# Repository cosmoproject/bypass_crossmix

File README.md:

# bypass_crossmix
Relay stereo bypass and crossmixer

Crossmixer connection: Turn the pot completely to what you want to be "wet", and find the side where
there is 0ohm to the center pin. This pin should be connected to pin 1 on the drywet on the PCB.

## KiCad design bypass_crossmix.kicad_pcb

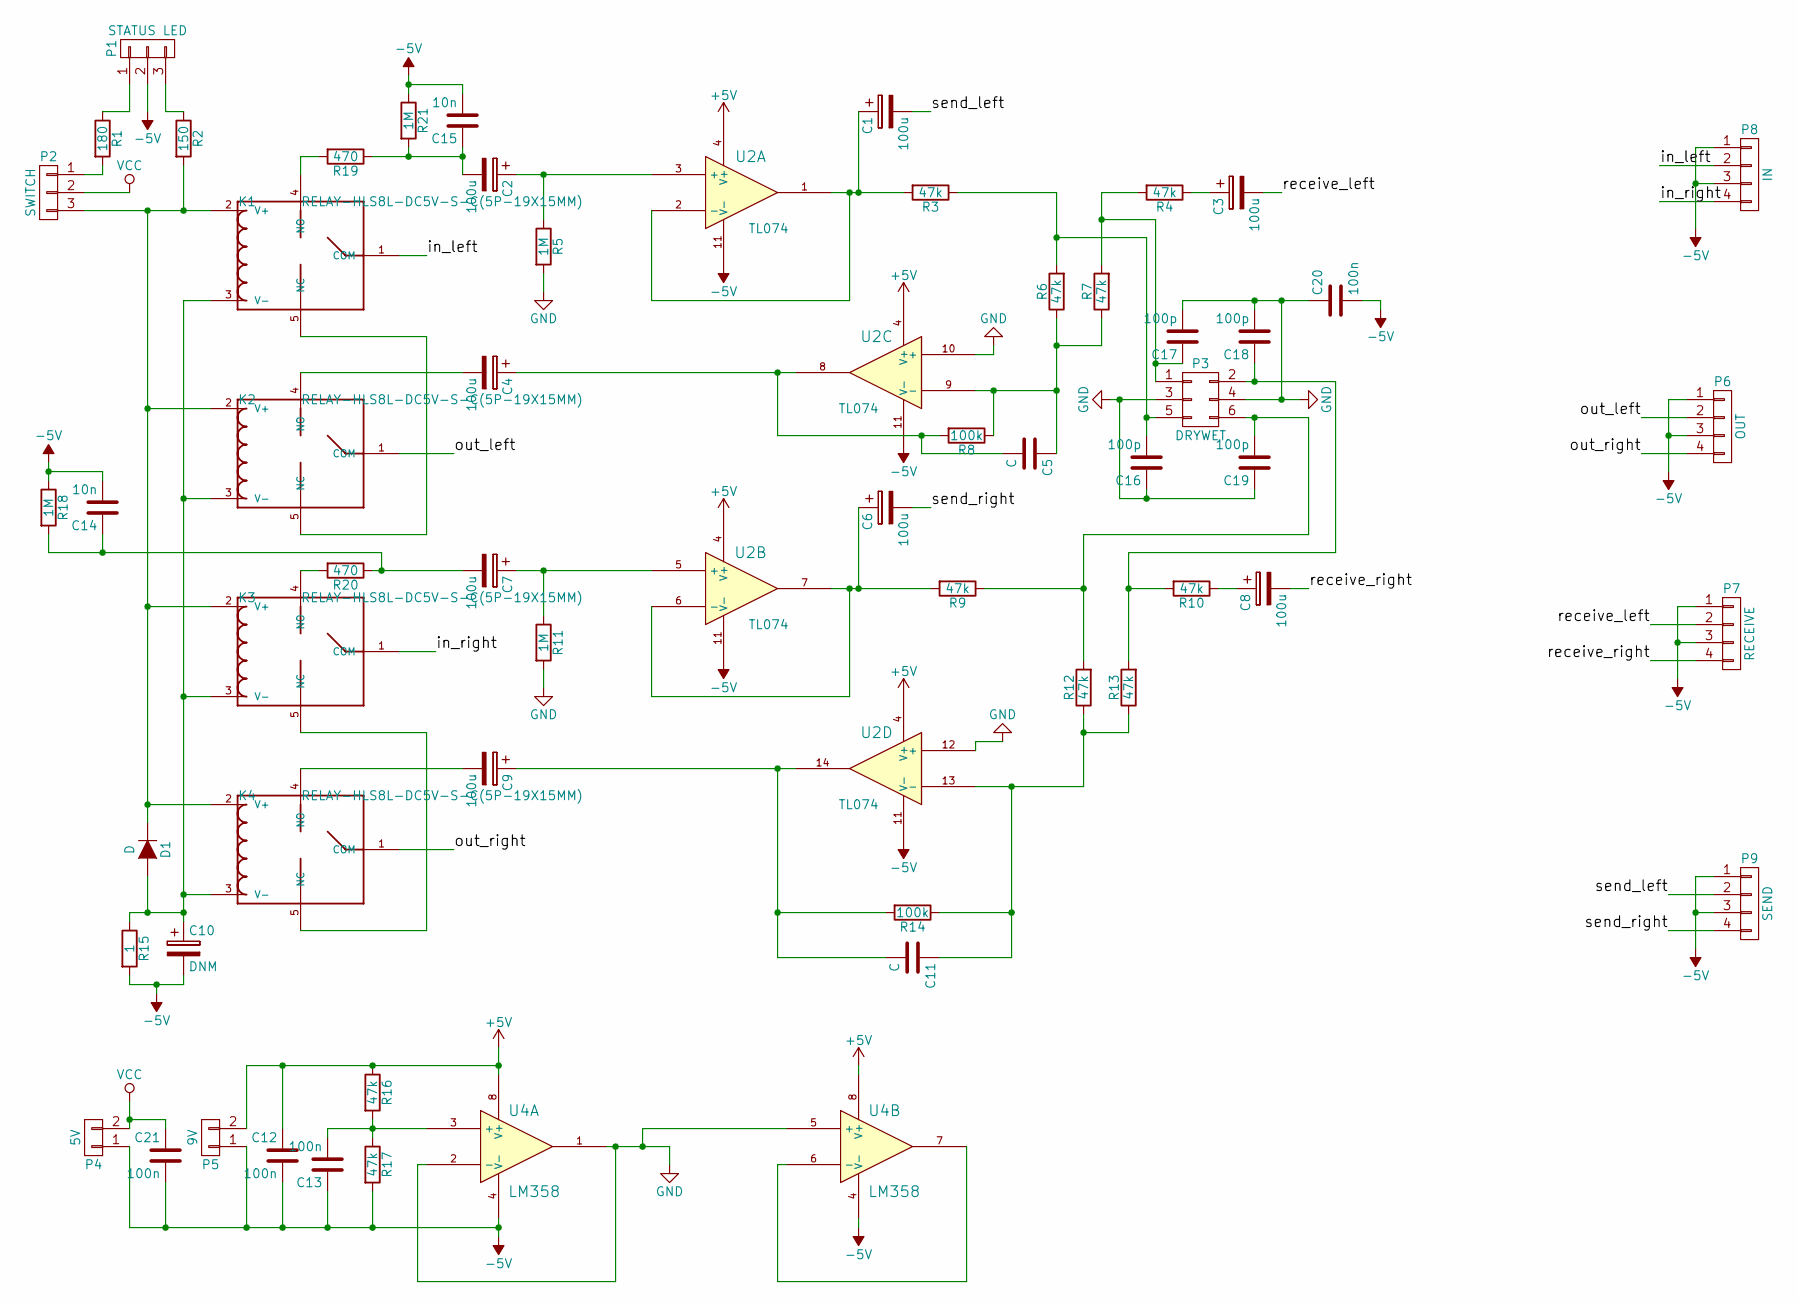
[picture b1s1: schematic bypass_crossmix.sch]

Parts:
C1, C2, C3, C4, C6, C7, C8, C9: 100u; Elko_vert_11x5mm_RM2.5_CopperClear
C5, C11: C; C_0603_HandSoldering
C10: DNM; Elko_vert_11x5mm_RM2.5_CopperClear
C12, C13, C20, C21: 100n; C_0603_HandSoldering
C14, C15: 10n; C_0603_HandSoldering
C16, C17, C18, C19: 100p; C_0603_HandSoldering
D1: D; DO-214AC
K1, K2, K3, K4: RELAY-HLS8L-DC5V-S-C(5P-19X15MM); REY5-19.0X15.0X15.0MM
P1: STATUS LED; Pin_Header_Straight_1x03
P2: SWITCH; Pin_Header_Straight_1x03
P3: DRYWET; Pin_Header_Straight_2x03
P4: 5V; Pin_Header_Straight_1x02
P5: 9V; Pin_Header_Straight_1x02
P6: OUT; Pin_Header_Straight_1x04
P7: RECEIVE; Pin_Header_Straight_1x04
P8: IN; Pin_Header_Straight_1x04
P9: SEND; Pin_Header_Straight_1x04
R1: 180; R_0603_HandSoldering
R2: 150; R_0603_HandSoldering
R3, R4, R6, R7, R9, R10, R12, R13, R16, R17: 47k; R_0603_HandSoldering
R5, R11, R18, R21: 1M; R_0603_HandSoldering
R8, R14: 100k; R_0603_HandSoldering
R15: 1; R_0603_HandSoldering
R19, R20: 470; R_0603_HandSoldering
U2: TL074; SOIC-14_3.9x8.7mm_Pitch1.27mm
U4: LM358; SOIC-8_3.9x4.9mm_Pitch1.27mm

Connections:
+5V: C12.1, P5.2, R16.1, U2.4 (V+), U4.8 (V+)
-5V: C10.2, C12.2, C13.1, C14.2, C15.2, C20.2, C21.2, P1.2, P4.1, P5.1, P6.1, P6.3, P7.1, P7.3, P8.1, P8.3, P9.1, P9.3, R15.2, R17.2, R18.1, R21.1, U2.11 (V-), U4.4 (V-)
/in_left: K1.1 (COM), P8.2
/in_right: K3.1 (COM), P8.4
/out_left: K2.1 (COM), P6.2
/out_right: K4.1 (COM), P6.4
/receive_left: C3.2, P7.2
/receive_right: C8.2, P7.4
/send_left: C1.2, P9.2
/send_right: C6.2, P9.4
GND: C16.1, C17.2, C18.2, C19.1, C20.1, P3.3, P3.4, R5.2, R11.2, U2.10 (+), U2.12 (+), U4.1, U4.2 (-), U4.5 (+)
unnamed: C1.1, R3.2, U2.1, U2.2 (-)
unnamed: C2.1, R5.1, U2.3 (+)
unnamed: C3.1, R4.1
unnamed: C4.1, C5.2, R8.2, U2.8
unnamed: C4.2, K2.4 (NO)
unnamed: C5.1, R6.1, R7.1, R8.1, U2.9 (-)
unnamed: C6.1, R9.2, U2.6 (-), U2.7
unnamed: C7.1, R11.1, U2.5 (+)
unnamed: C8.1, R10.1
unnamed: C9.2, K4.4 (NO)
unnamed: C10.1, D1.2 (A), K1.3 (V-), K2.3 (V-), K3.3 (V-), K4.3 (V-), R15.1
unnamed: C11.1, R12.1, R13.1, R14.1, U2.13 (-)
unnamed: C9.1, C11.2, R14.2, U2.14
unnamed: C13.2, R16.2, R17.1, U4.3 (+)
unnamed: C7.2, C14.1, R18.2, R20.1
unnamed: C2.2, C15.1, R19.1, R21.2
unnamed: C16.2, P3.5, R3.1, R6.2
unnamed: C17.1, P3.1, R4.2, R7.2
unnamed: C18.1, P3.2, R10.2, R13.2
unnamed: C19.2, P3.6, R9.1, R12.2
unnamed: D1.1 (K), K1.2 (V+), K2.2 (V+), K3.2 (V+), K4.2 (V+), P2.3, R2.2
unnamed: K1.4 (NO), R19.2
unnamed: K1.5 (NC), K2.5 (NC)
unnamed: K3.4 (NO), R20.2
unnamed: K3.5 (NC), K4.5 (NC)
unnamed: P1.1, R1.1
unnamed: P1.3, R2.1
unnamed: P2.1, R1.2
unnamed: U4.6 (-), U4.7
VCC: C21.1, P2.2, P4.2

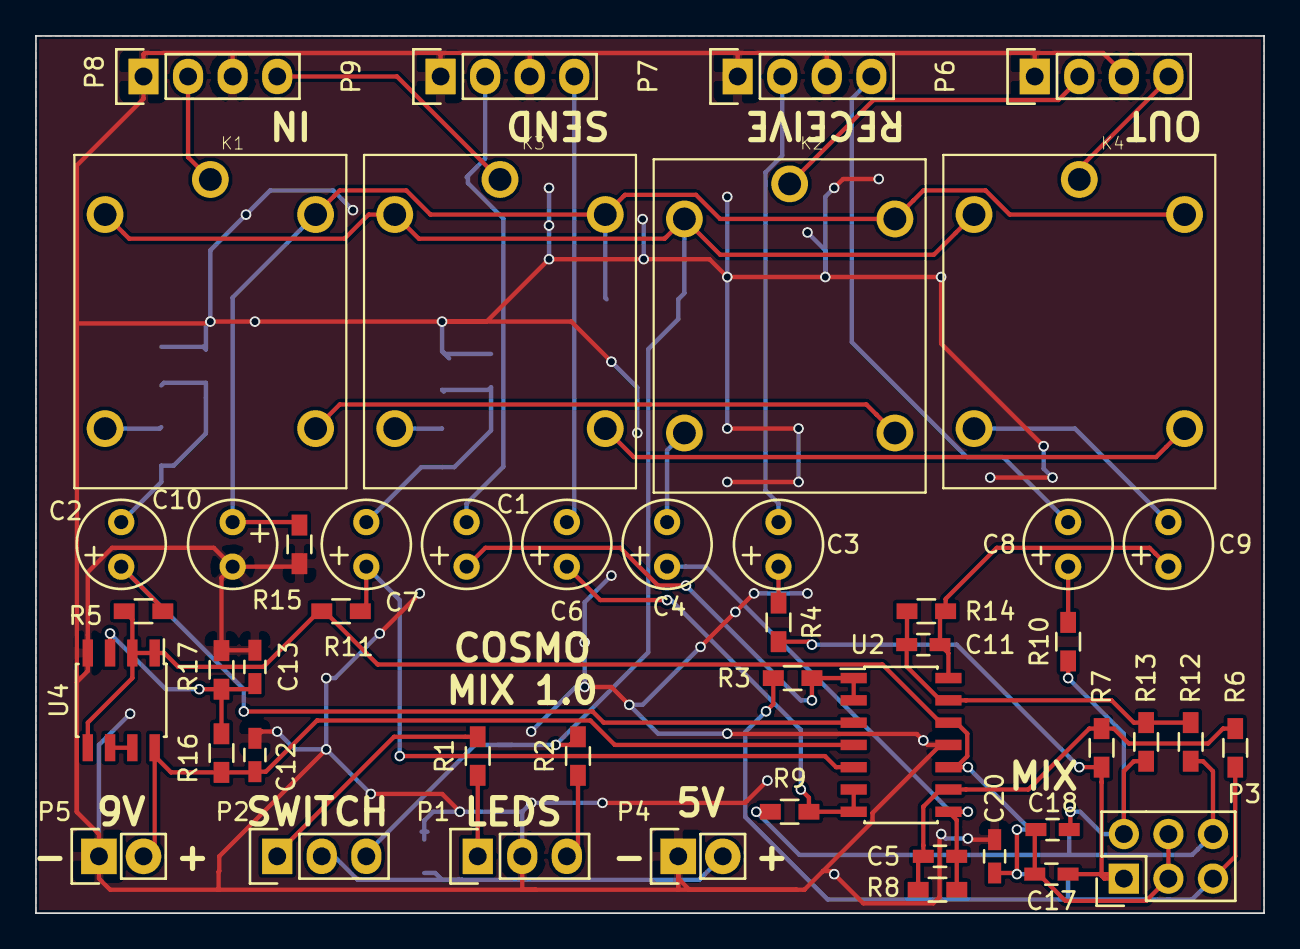
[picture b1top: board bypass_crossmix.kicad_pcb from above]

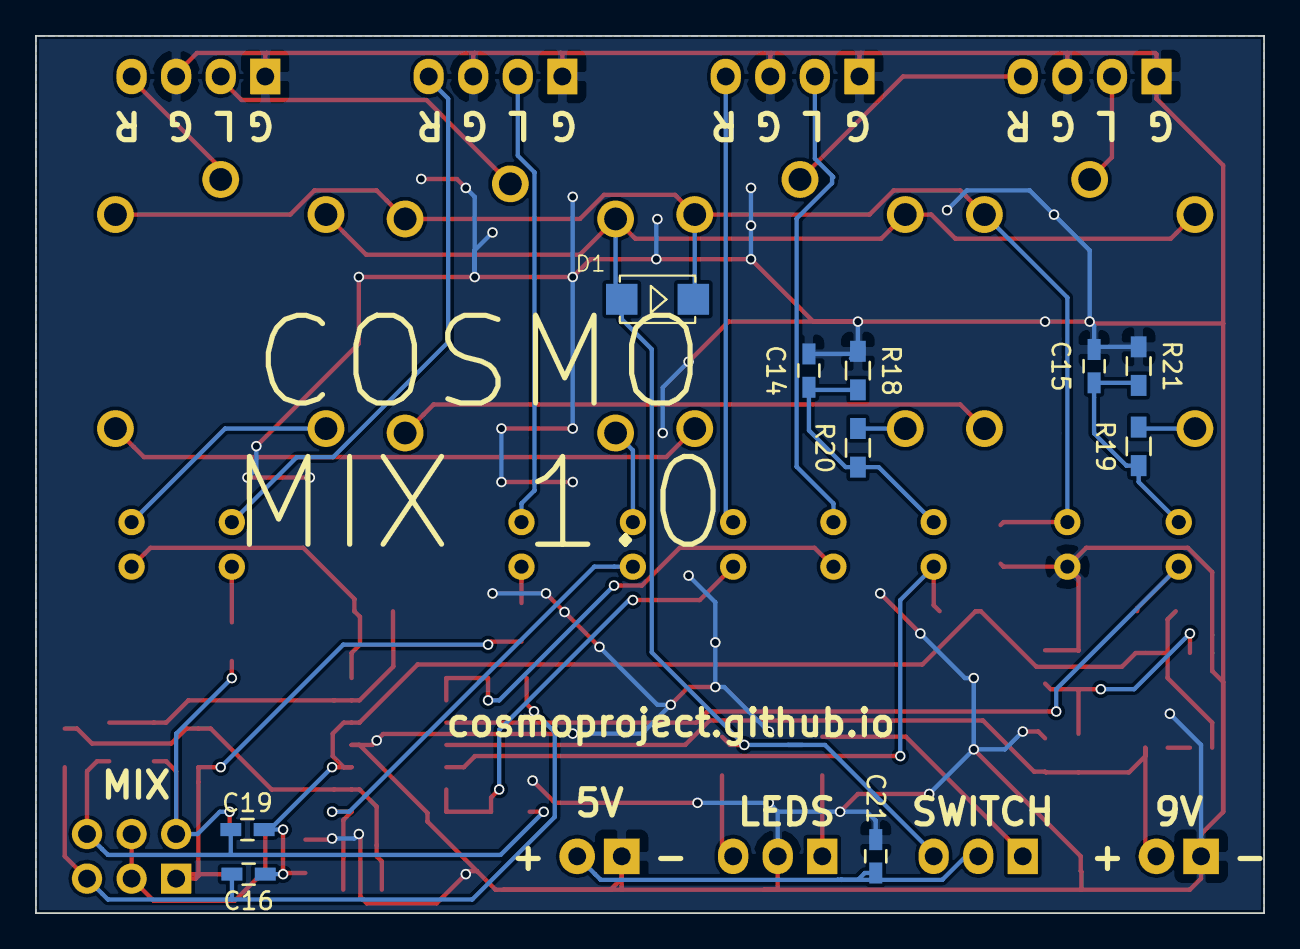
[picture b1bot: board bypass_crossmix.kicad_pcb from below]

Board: 2 copper layers, 70.0 x 50.0 mm, 58 parts (10 on the bottom side), 41 nets.

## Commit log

2016-08-27 Latest changes
2016-08-27 Generate PDF
